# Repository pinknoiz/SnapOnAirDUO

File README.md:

# SnapOnAirDUO
Small  ESP32 RFM95 Dual Display Lora Communicator (Dr CADIC)

COLOR Display is here: https://fr.aliexpress.com/item/Nouveau-IPS-1-3-pouces-3-3-V-12PIN-SPI-HD-cran-d-affichage-TFT-couleur/32859374478.html
OLED Display is here: https://fr.aliexpress.com/item/0-91-inch-128x32-I2C-IIC-Serial-Blue-OLED-LCD-Display-Module-0-91-12832-SSD1306/32758264797.html
Buzzer is here: https://fr.aliexpress.com/item/10pcs-lot-3V-5V-ultra-small-SMD-active-patch-buzzer-9-6mm-9-6mm-5mm-square/32783296014.html
Buttons are here: https://fr.aliexpress.com/item/Free-shipping-50pcs-lot-6-6-5-SMD-Silent-buttons-The-silicone-keypad-6x6x5mm-best-quality/32820232659.html
ESP32 BOard is here: https://fr.aliexpress.com/item/TTGO-ESP32-Dev-Module-WiFi-Bluetooth-4MB-Flash/32813561581.html
RFM95 is here: https://fr.aliexpress.com/item/2PCS-LOT-RFM95-RFM95W-868Mhz-915Mhz-RFM95-868MHz-RFM95-915MHz-LoRaTM-Wireless-Transceiver/32817685871.html
All Resistors are 1206
All Capacitors are 1206
Switch is PSPDT_CM12

Have fun !!!

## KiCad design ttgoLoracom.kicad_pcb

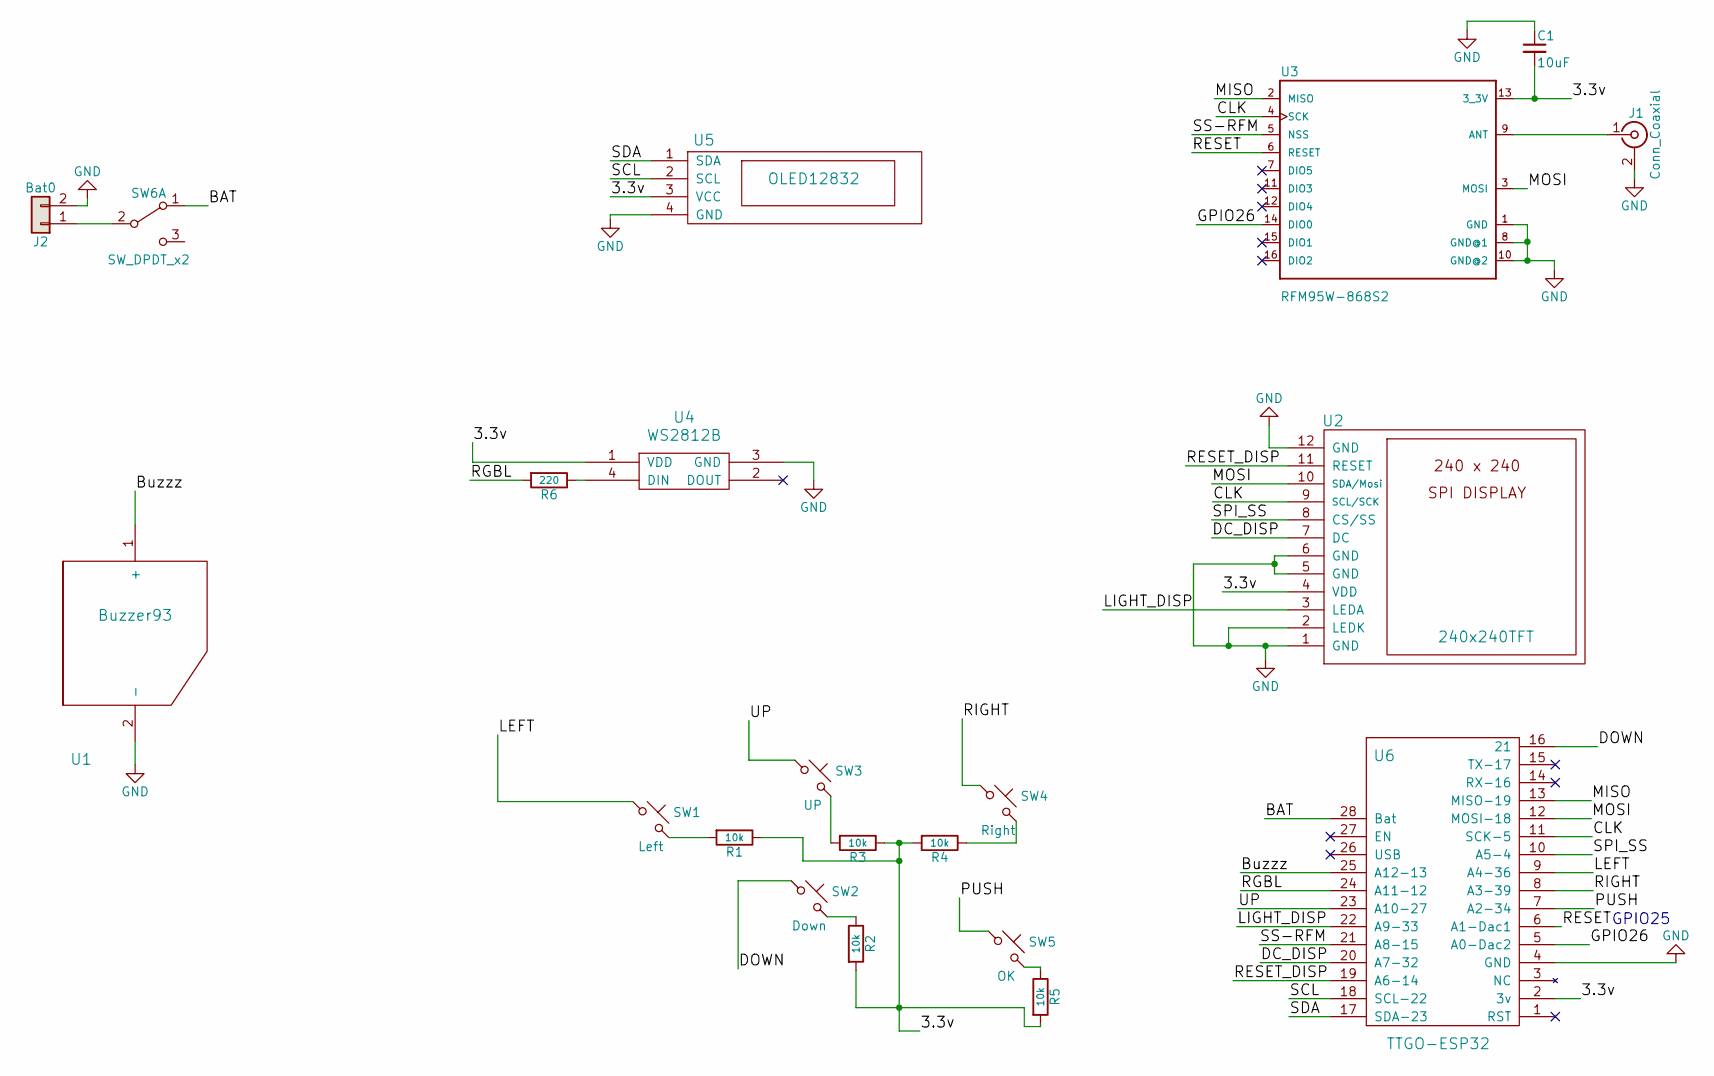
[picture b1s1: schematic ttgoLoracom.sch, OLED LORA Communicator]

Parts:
C1: 10uF; C_1206_HandSoldering
J1: Conn_Coaxial; SMA_EDGE
J2: Bat0; Socket_Strip_Straight_1x02_Pitch2.54mm
R1, R2, R3, R4, R5: 10k; R_1206_HandSoldering
R6: 220; R_1206_HandSoldering
SW1: Left; SW_TP1003
SW2: Down; SW_TP1003
SW3: UP; SW_TP1003
SW4: Right; SW_TP1003
SW5: OK; SW_TP1003
SW6: SW_DPDT_x2; SW_SPDT_PCM12
U1: Buzzer93; BuzzerActive2
U2: 240x240TFT; 240240TFT
U3: RFM95W-868S2; RFM95W
U4: WS2812B
U5: OLED12832; OLED-0.91-128x32
U6: TTGO-ESP32

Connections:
/3.3v: C1.2, R1.1, R2.2, R3.1, R4.2, R5.2, U2.4 (VDD), U3.13 (3_3V), U4.1 (VDD), U5.3 (VCC), U6.2 (3v)
/BAT: SW6.1 (A), U6.28 (Bat)
/Buzzz: U1.1 (+), U6.25 (A12-13)
/CLK: U2.9 (SCL/SCK), U3.4 (SCK), U6.11 (SCK-5)
/DC_DISP: U2.7 (DC), U6.20 (A7-32)
/DOWN: SW2.1, U6.16 (21)
/GPIO26: U3.14 (DIO0), U6.5 (A0-Dac2)
/LEFT: SW1.1, U6.9 (A4-36)
/LIGHT_DISP: U2.3 (LEDA), U6.22 (A9-33)
/MISO: U3.2 (MISO), U6.13 (MISO-19)
/MOSI: U2.10 (SDA/Mosi), U3.3 (MOSI), U6.12 (MOSI-18)
/PUSH: SW5.1, U6.7 (A2-34)
/RESET: U3.6 (RESET), U6.6 (A1-Dac1)
/RESET_DISP: U2.11 (RESET), U6.19 (A6-14)
/RGBL: R6.2, U6.24 (A11-12)
/RIGHT: SW4.1, U6.8 (A3-39)
/SCL: U5.2 (SCL), U6.18 (SCL-22)
/SDA: U5.1 (SDA), U6.17 (SDA-23)
/SPI_SS: U2.8 (CS/SS), U6.10 (A5-4)
/SS-RFM: U3.5 (NSS), U6.21 (A8-15)
/UP: SW3.1, U6.23 (A10-27)
GND: C1.1, J1.2 (Ext), J2.2, U1.2 (-), U2.1 (GND), U2.2 (LEDK), U2.5 (GND), U2.6 (GND), U2.12 (GND), U3.1 (GND), U3.8 (GND@1), U3.10 (GND@2), U4.3 (GND), U5.4 (GND), U6.4 (GND)
unnamed: J1.1 (In), U3.9 (ANT)
unnamed: J2.1, SW6.2 (B)
unnamed: R1.2, SW1.2
unnamed: R2.1, SW2.2
unnamed: R3.2, SW3.2
unnamed: R4.1, SW4.2
unnamed: R5.1, SW5.2
unnamed: R6.1, U4.4 (DIN)

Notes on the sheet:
GPIO25

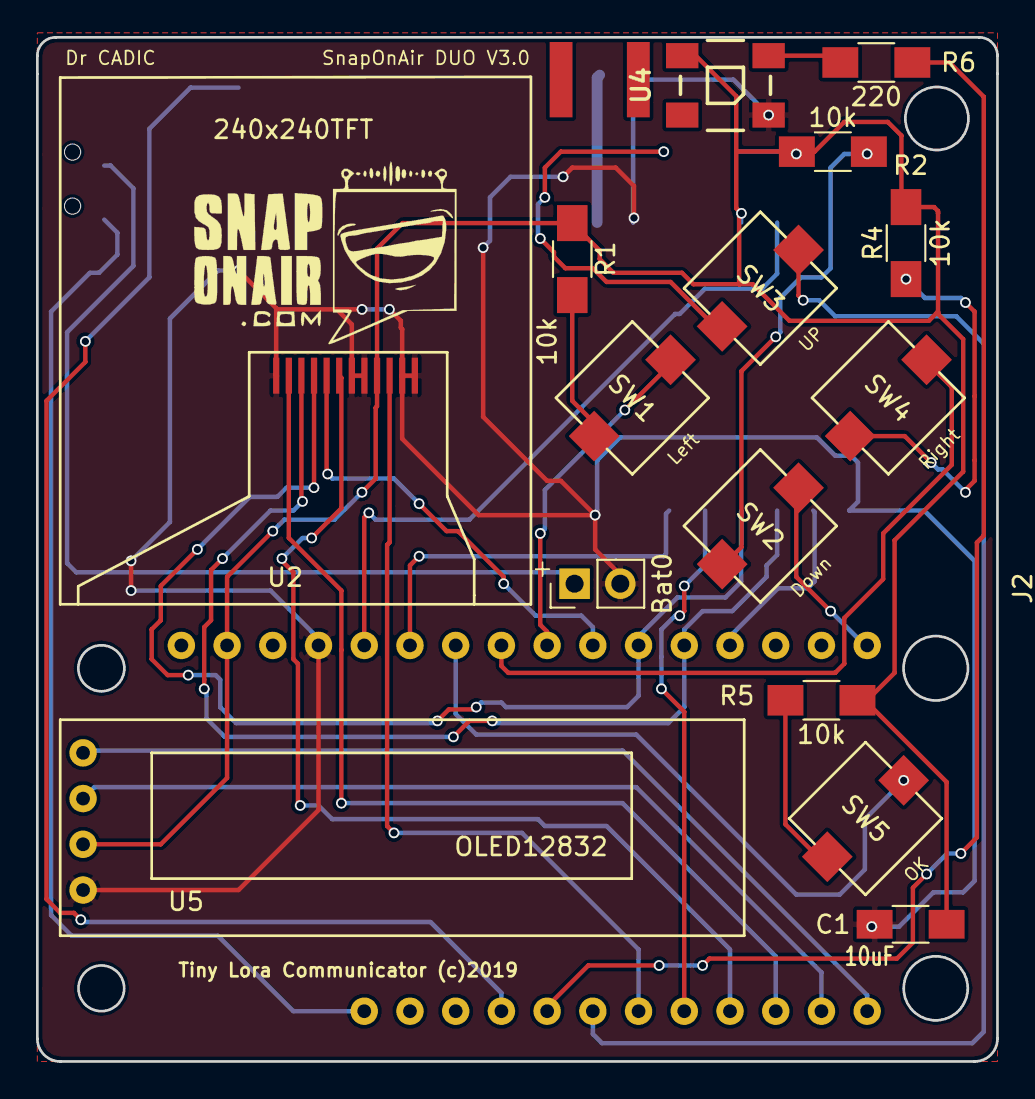
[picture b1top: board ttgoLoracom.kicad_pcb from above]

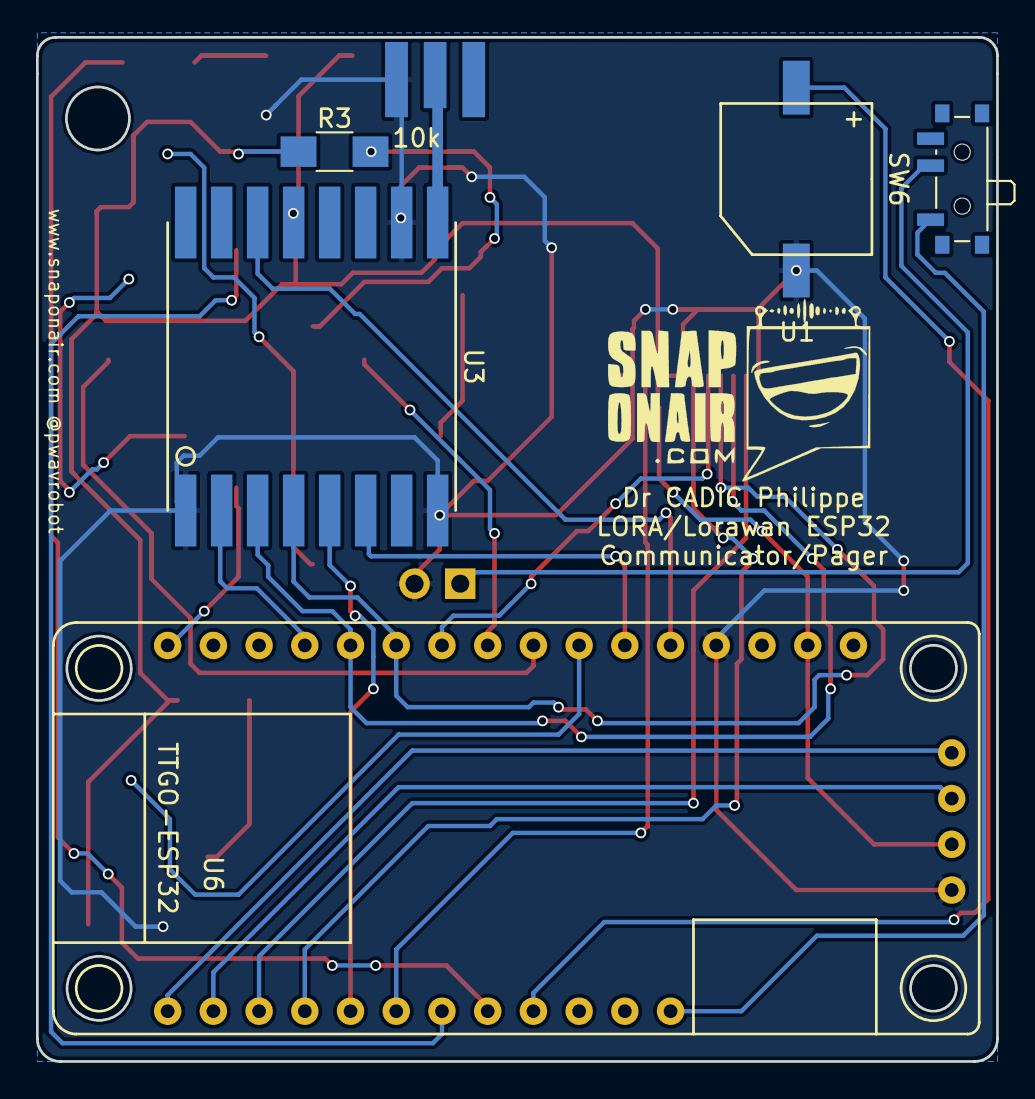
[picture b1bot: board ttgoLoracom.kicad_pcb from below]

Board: 2 copper layers, 53.3 x 56.9 mm, 21 parts (6 on the bottom side), 30 nets.

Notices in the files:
ttgoLoracom.kicad_pcb:
Tiny Lora Communicator (c)2019
